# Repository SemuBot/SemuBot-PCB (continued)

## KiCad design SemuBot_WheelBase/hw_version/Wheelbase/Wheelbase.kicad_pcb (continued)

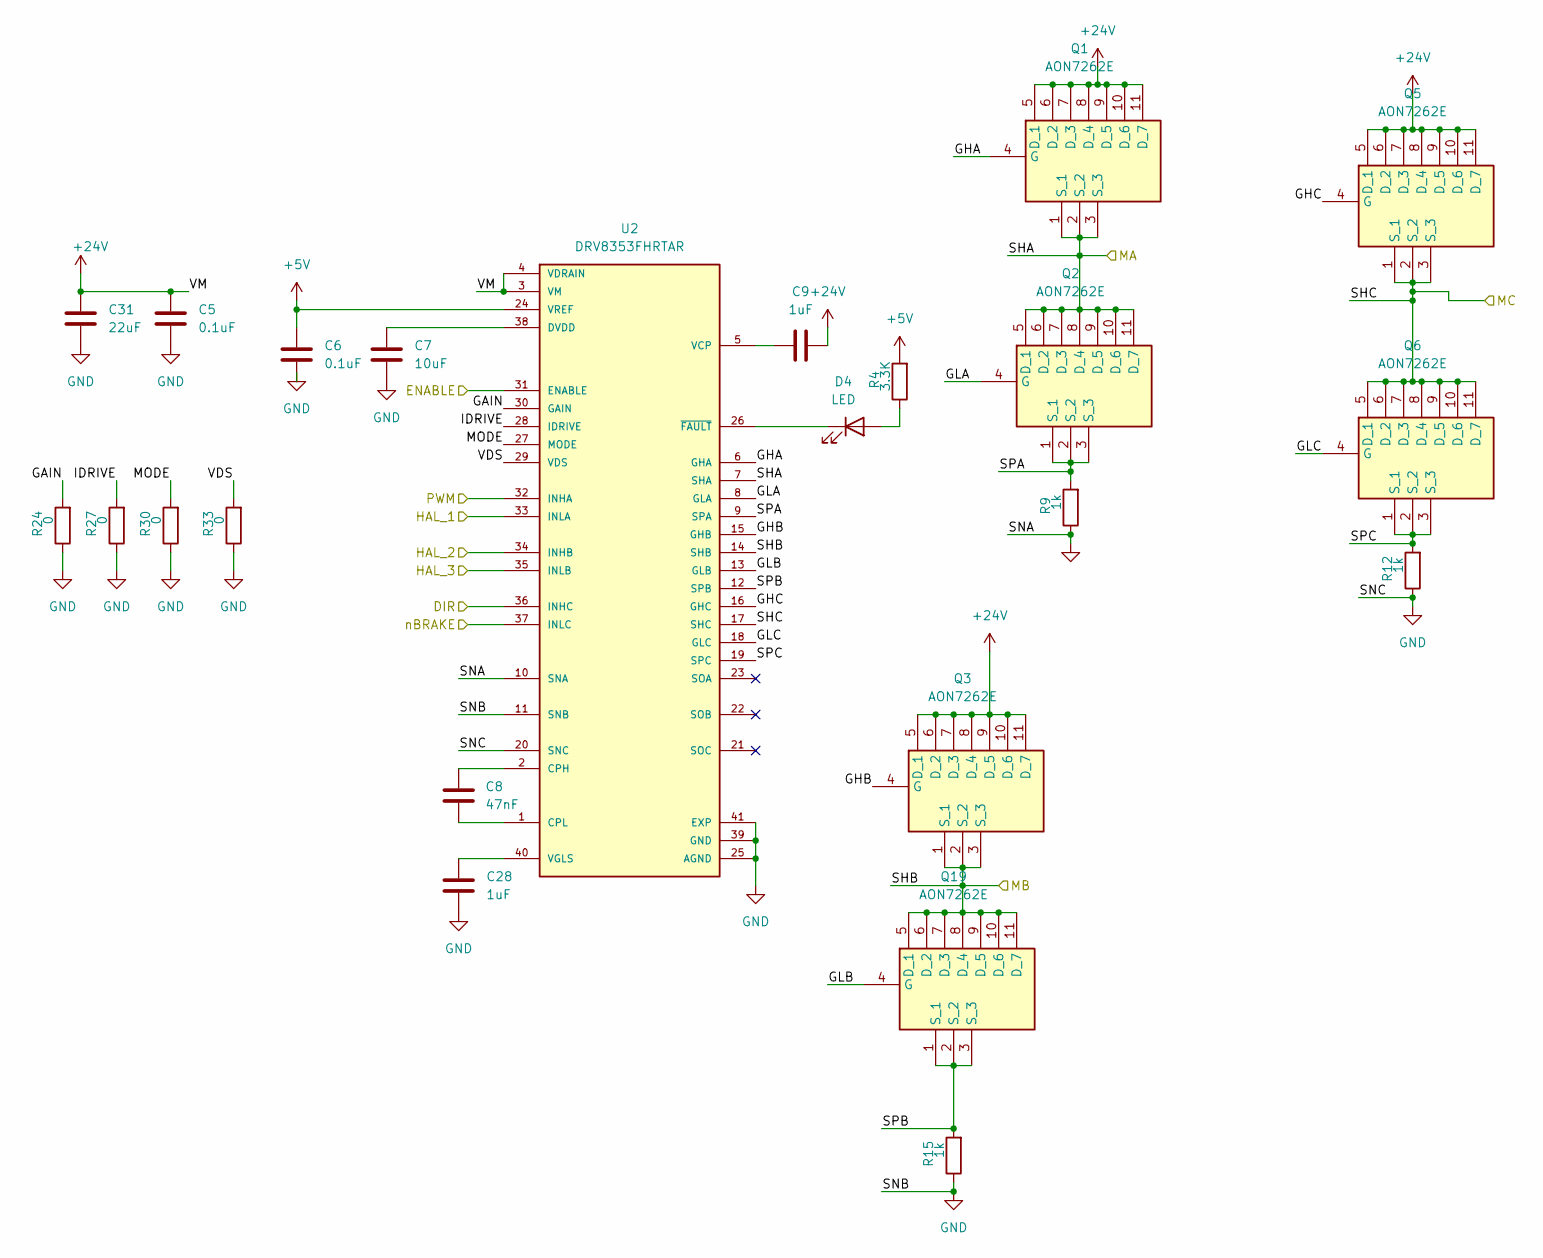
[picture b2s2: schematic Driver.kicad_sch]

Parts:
C5, C6: 0.1uF; C_0603_1608Metric_Pad1.08x0.95mm_HandSolder
C7: 10uF; C_0603_1608Metric_Pad1.08x0.95mm_HandSolder
C8: 47nF; C_0603_1608Metric_Pad1.08x0.95mm_HandSolder
C9, C28: 1uF; C_0603_1608Metric_Pad1.08x0.95mm_HandSolder
C31: 22uF; C_0805_2012Metric_Pad1.18x1.45mm_HandSolder
D4: LED; LED_0603_1608Metric_Pad1.05x0.95mm_HandSolder
Q1, Q2, Q3, Q5, Q6, Q19: AON7262E; Manufacturer_Part_Number AON7262E
R4: 3.3K; R_0603_1608Metric_Pad0.98x0.95mm_HandSolder
R9, R12, R15: 1k; R_0603_1608Metric_Pad0.98x0.95mm_HandSolder
R24, R27, R30, R33: 0; R_0603_1608Metric_Pad0.98x0.95mm_HandSolder
U2: DRV8353FHRTAR; QFN50P600X600X80-41N; PARTREV A

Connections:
+5V: C6.1, R4.2, U2.24 (VREF); also elsewhere on the board
+24V: C5.1, C9.2, C31.2, Q1.5 (D_1), Q1.6 (D_2), Q1.7 (D_3), Q1.8 (D_4), Q1.9 (D_5), Q1.10 (D_6), Q1.11 (D_7), Q3.5 (D_1), Q3.6 (D_2), Q3.7 (D_3), Q3.8 (D_4), Q3.9 (D_5), Q3.10 (D_6), Q3.11 (D_7), Q5.5 (D_1), Q5.6 (D_2), Q5.7 (D_3), Q5.8 (D_4), Q5.9 (D_5), Q5.10 (D_6), Q5.11 (D_7), U2.3 (VM), U2.4 (VDRAIN); also elsewhere on the board
/ENABLE: U2.31 (ENABLE); also elsewhere on the board
/MOTOR1_DIR: U2.36 (INHC); also elsewhere on the board
/MOTOR1_PWM: U2.32 (INHA); also elsewhere on the board
/Motor_1/GAIN: R24.2, U2.30 (GAIN)
/Motor_1/GHA: Q1.4 (G), U2.6 (GHA)
/Motor_1/GHB: Q3.4 (G), U2.15 (GHB)
/Motor_1/GHC: Q5.4 (G), U2.16 (GHC)
/Motor_1/GLA: Q2.4 (G), U2.8 (GLA)
/Motor_1/GLB: Q19.4 (G), U2.13 (GLB)
/Motor_1/GLC: Q6.4 (G), U2.18 (GLC)
/Motor_1/HAL_1: U2.33 (INLA); also elsewhere on the board
/Motor_1/HAL_2: U2.34 (INHB); also elsewhere on the board
/Motor_1/HAL_3: U2.35 (INLB); also elsewhere on the board
/Motor_1/IDRIVE: R27.2, U2.28 (IDRIVE)
/Motor_1/MODE: R30.2, U2.27 (MODE)
/Motor_1/SHA: Q1.1 (S_1), Q1.2 (S_2), Q1.3 (S_3), Q2.5 (D_1), Q2.6 (D_2), Q2.7 (D_3), Q2.8 (D_4), Q2.9 (D_5), Q2.10 (D_6), Q2.11 (D_7), U2.7 (SHA); also elsewhere on the board
/Motor_1/SHB: Q3.1 (S_1), Q3.2 (S_2), Q3.3 (S_3), Q19.5 (D_1), Q19.6 (D_2), Q19.7 (D_3), Q19.8 (D_4), Q19.9 (D_5), Q19.10 (D_6), Q19.11 (D_7), U2.14 (SHB); also elsewhere on the board
/Motor_1/SHC: Q5.1 (S_1), Q5.2 (S_2), Q5.3 (S_3), Q6.5 (D_1), Q6.6 (D_2), Q6.7 (D_3), Q6.8 (D_4), Q6.9 (D_5), Q6.10 (D_6), Q6.11 (D_7), U2.17 (SHC); also elsewhere on the board
/Motor_1/SPA: Q2.1 (S_1), Q2.2 (S_2), Q2.3 (S_3), R9.2, U2.9 (SPA)
/Motor_1/SPB: Q19.1 (S_1), Q19.2 (S_2), Q19.3 (S_3), R15.2, U2.12 (SPB)
/Motor_1/SPC: Q6.1 (S_1), Q6.2 (S_2), Q6.3 (S_3), R12.2, U2.19 (SPC)
/Motor_1/VDS: R33.2, U2.29 (VDS)
/nBRAKE: U2.37 (INLC); also elsewhere on the board
GND: C5.2, C6.2, C7.2, C28.1, C31.1, R9.1, R12.1, R15.1, R24.1, R27.1, R30.1, R33.1, U2.10 (SNA), U2.11 (SNB), U2.20 (SNC), U2.25 (AGND), U2.39 (GND), U2.41 (EXP); also elsewhere on the board
unnamed: D4.2 (A), R4.1
unnamed: D4.1 (K), U2.26 (~FAULT)
unnamed: C8.1, U2.2 (CPH)
unnamed: C8.2, U2.1 (CPL)
unnamed: C7.1, U2.38 (DVDD)
unnamed: C9.1, U2.5 (VCP)
unnamed: C28.2, U2.40 (VGLS)

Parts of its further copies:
C17, C18, C23, C24: 0.1uF; C_0603_1608Metric_Pad1.08x0.95mm_HandSolder
C19, C25: 10uF; C_0603_1608Metric_Pad1.08x0.95mm_HandSolder
C20, C26: 47nF; C_0603_1608Metric_Pad1.08x0.95mm_HandSolder
C21, C27, C29, C30: 1uF; C_0603_1608Metric_Pad1.08x0.95mm_HandSolder
C32, C33: 22uF; C_0805_2012Metric_Pad1.18x1.45mm_HandSolder
D5, D6: LED; LED_0603_1608Metric_Pad1.05x0.95mm_HandSolder
Q4, Q7, Q8, Q9, Q10, Q11, Q12, Q13, Q14, Q15, Q20, Q21: AON7262E; Manufacturer_Part_Number AON7262E
R7, R8: 3.3K; R_0603_1608Metric_Pad0.98x0.95mm_HandSolder
R10, R11, R13, R14, R16, R17: 1k; R_0603_1608Metric_Pad0.98x0.95mm_HandSolder
R25, R26, R28, R29, R31, R32, R34, R35: 0; R_0603_1608Metric_Pad0.98x0.95mm_HandSolder
U3, U4: DRV8353FHRTAR; QFN50P600X600X80-41N; PARTREV A

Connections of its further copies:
+5V: C18.1, C24.1, R7.2, R8.2, U3.24 (VREF), U4.24 (VREF); also elsewhere on the board
+24V: C17.1, C21.2, C23.1, C27.2, C32.2, C33.2, Q4.5 (D_1), Q4.6 (D_2), Q4.7 (D_3), Q4.8 (D_4), Q4.9 (D_5), Q4.10 (D_6), Q4.11 (D_7), Q7.5 (D_1), Q7.6 (D_2), Q7.7 (D_3), Q7.8 (D_4), Q7.9 (D_5), Q7.10 (D_6), Q7.11 (D_7), Q9.5 (D_1), Q9.6 (D_2), Q9.7 (D_3), Q9.8 (D_4), Q9.9 (D_5), Q9.10 (D_6), Q9.11 (D_7), Q11.5 (D_1), Q11.6 (D_2), Q11.7 (D_3), Q11.8 (D_4), Q11.9 (D_5), Q11.10 (D_6), Q11.11 (D_7), Q13.5 (D_1), Q13.6 (D_2), Q13.7 (D_3), Q13.8 (D_4), Q13.9 (D_5), Q13.10 (D_6), Q13.11 (D_7), Q15.5 (D_1), Q15.6 (D_2), Q15.7 (D_3), Q15.8 (D_4), Q15.9 (D_5), Q15.10 (D_6), Q15.11 (D_7), U3.3 (VM), U3.4 (VDRAIN), U4.3 (VM), U4.4 (VDRAIN); also elsewhere on the board
/ENABLE: U3.31 (ENABLE), U4.31 (ENABLE); also elsewhere on the board
/MOTOR2_DIR: U3.36 (INHC); also elsewhere on the board
/MOTOR2_PWM: U3.32 (INHA); also elsewhere on the board
/MOTOR3_DIR: U4.36 (INHC); also elsewhere on the board
/MOTOR3_PWM: U4.32 (INHA); also elsewhere on the board
/Motor_2/GAIN: R25.2, U3.30 (GAIN)
/Motor_2/GHA: Q7.4 (G), U3.6 (GHA)
/Motor_2/GHB: Q4.4 (G), U3.15 (GHB)
/Motor_2/GHC: Q11.4 (G), U3.16 (GHC)
/Motor_2/GLA: Q8.4 (G), U3.8 (GLA)
/Motor_2/GLB: Q20.4 (G), U3.13 (GLB)
/Motor_2/GLC: Q10.4 (G), U3.18 (GLC)
/Motor_2/HAL_1: U3.33 (INLA); also elsewhere on the board
/Motor_2/HAL_2: U3.34 (INHB); also elsewhere on the board
/Motor_2/HAL_3: U3.35 (INLB); also elsewhere on the board
/Motor_2/IDRIVE: R28.2, U3.28 (IDRIVE)
/Motor_2/MODE: R31.2, U3.27 (MODE)
/Motor_2/SHA: Q7.1 (S_1), Q7.2 (S_2), Q7.3 (S_3), Q8.5 (D_1), Q8.6 (D_2), Q8.7 (D_3), Q8.8 (D_4), Q8.9 (D_5), Q8.10 (D_6), Q8.11 (D_7), U3.7 (SHA); also elsewhere on the board
/Motor_2/SHB: Q4.1 (S_1), Q4.2 (S_2), Q4.3 (S_3), Q20.5 (D_1), Q20.6 (D_2), Q20.7 (D_3), Q20.8 (D_4), Q20.9 (D_5), Q20.10 (D_6), Q20.11 (D_7), U3.14 (SHB); also elsewhere on the board
/Motor_2/SHC: Q10.5 (D_1), Q10.6 (D_2), Q10.7 (D_3), Q10.8 (D_4), Q10.9 (D_5), Q10.10 (D_6), Q10.11 (D_7), Q11.1 (S_1), Q11.2 (S_2), Q11.3 (S_3), U3.17 (SHC); also elsewhere on the board
/Motor_2/SPA: Q8.1 (S_1), Q8.2 (S_2), Q8.3 (S_3), R10.2, U3.9 (SPA)
/Motor_2/SPB: Q20.1 (S_1), Q20.2 (S_2), Q20.3 (S_3), R16.2, U3.12 (SPB)
/Motor_2/SPC: Q10.1 (S_1), Q10.2 (S_2), Q10.3 (S_3), R13.2, U3.19 (SPC)
/Motor_2/VDS: R34.2, U3.29 (VDS)
/Motor_3/GAIN: R26.2, U4.30 (GAIN)
/Motor_3/GHA: Q13.4 (G), U4.6 (GHA)
/Motor_3/GHB: Q9.4 (G), U4.15 (GHB)
/Motor_3/GHC: Q15.4 (G), U4.16 (GHC)
/Motor_3/GLA: Q14.4 (G), U4.8 (GLA)
/Motor_3/GLB: Q21.4 (G), U4.13 (GLB)
/Motor_3/GLC: Q12.4 (G), U4.18 (GLC)
/Motor_3/HAL_1: U4.33 (INLA); also elsewhere on the board
/Motor_3/HAL_2: U4.34 (INHB); also elsewhere on the board
/Motor_3/HAL_3: U4.35 (INLB); also elsewhere on the board
/Motor_3/IDRIVE: R29.2, U4.28 (IDRIVE)
/Motor_3/MODE: R32.2, U4.27 (MODE)
/Motor_3/SHA: Q13.1 (S_1), Q13.2 (S_2), Q13.3 (S_3), Q14.5 (D_1), Q14.6 (D_2), Q14.7 (D_3), Q14.8 (D_4), Q14.9 (D_5), Q14.10 (D_6), Q14.11 (D_7), U4.7 (SHA); also elsewhere on the board
/Motor_3/SHB: Q9.1 (S_1), Q9.2 (S_2), Q9.3 (S_3), Q21.5 (D_1), Q21.6 (D_2), Q21.7 (D_3), Q21.8 (D_4), Q21.9 (D_5), Q21.10 (D_6), Q21.11 (D_7), U4.14 (SHB); also elsewhere on the board
/Motor_3/SHC: Q12.5 (D_1), Q12.6 (D_2), Q12.7 (D_3), Q12.8 (D_4), Q12.9 (D_5), Q12.10 (D_6), Q12.11 (D_7), Q15.1 (S_1), Q15.2 (S_2), Q15.3 (S_3), U4.17 (SHC); also elsewhere on the board
/Motor_3/SPA: Q14.1 (S_1), Q14.2 (S_2), Q14.3 (S_3), R11.2, U4.9 (SPA)
/Motor_3/SPB: Q21.1 (S_1), Q21.2 (S_2), Q21.3 (S_3), R17.2, U4.12 (SPB)
/Motor_3/SPC: Q12.1 (S_1), Q12.2 (S_2), Q12.3 (S_3), R14.2, U4.19 (SPC)
/Motor_3/VDS: R35.2, U4.29 (VDS)
/nBRAKE: U3.37 (INLC), U4.37 (INLC); also elsewhere on the board
GND: C17.2, C18.2, C19.2, C23.2, C24.2, C25.2, C29.1, C30.1, C32.1, C33.1, R10.1, R11.1, R13.1, R14.1, R16.1, R17.1, R25.1, R26.1, R28.1, R29.1, R31.1, R32.1, R34.1, R35.1, U3.10 (SNA), U3.11 (SNB), U3.20 (SNC), U3.25 (AGND), U3.39 (GND), U3.41 (EXP), U4.10 (SNA), U4.11 (SNB), U4.20 (SNC), U4.25 (AGND), U4.39 (GND), U4.41 (EXP); also elsewhere on the board
unnamed: D5.2 (A), R7.1
unnamed: D5.1 (K), U3.26 (~FAULT)
unnamed: D6.2 (A), R8.1
unnamed: D6.1 (K), U4.26 (~FAULT)
unnamed: C20.1, U3.2 (CPH)
unnamed: C20.2, U3.1 (CPL)
unnamed: C19.1, U3.38 (DVDD)
unnamed: C21.1, U3.5 (VCP)
unnamed: C29.2, U3.40 (VGLS)
unnamed: C26.1, U4.2 (CPH)
unnamed: C26.2, U4.1 (CPL)
unnamed: C25.1, U4.38 (DVDD)
unnamed: C27.1, U4.5 (VCP)
unnamed: C30.2, U4.40 (VGLS)

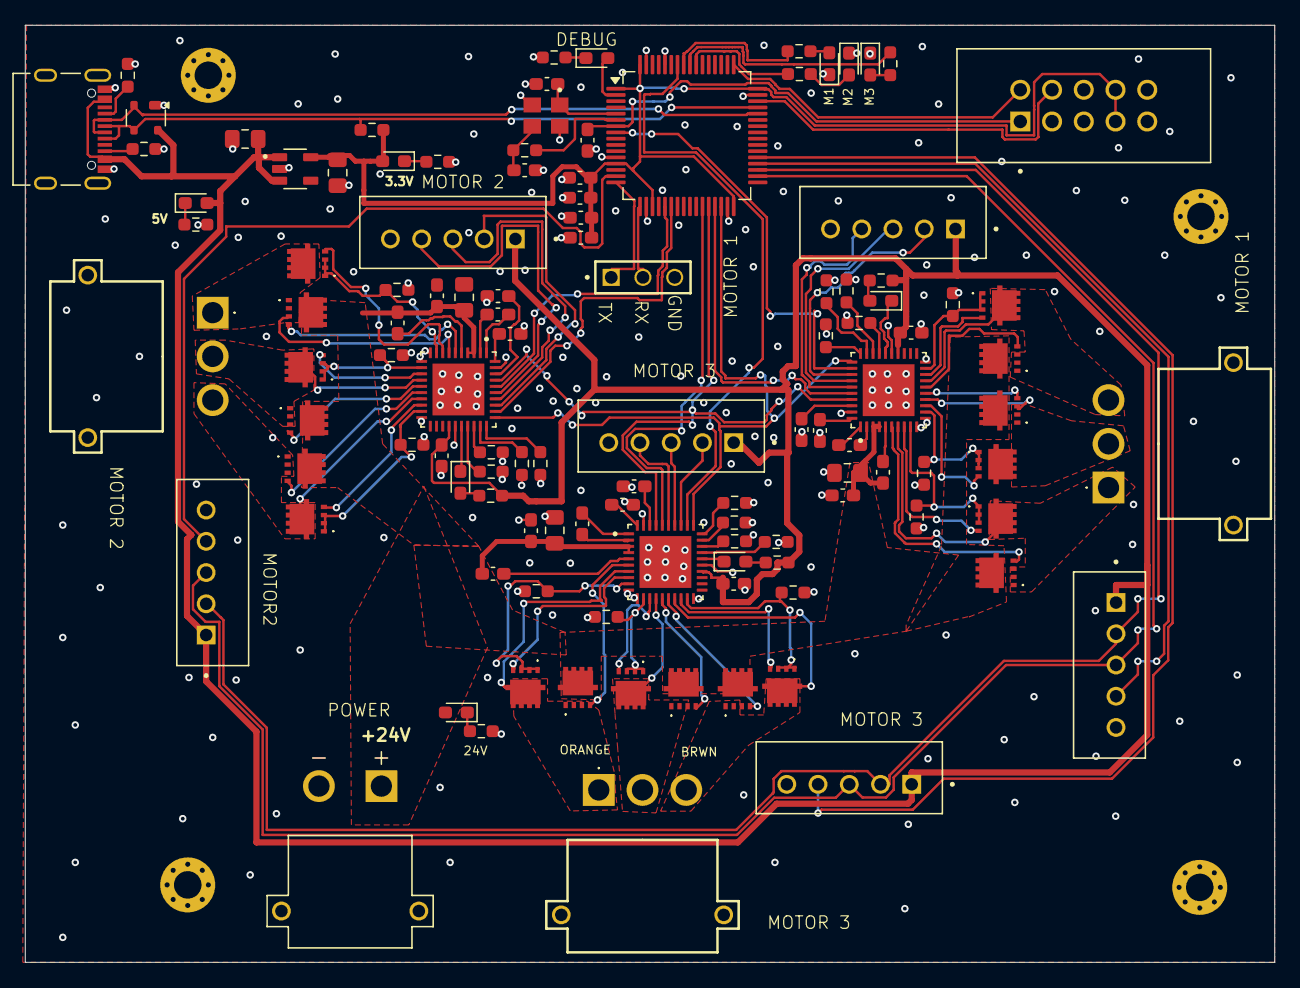
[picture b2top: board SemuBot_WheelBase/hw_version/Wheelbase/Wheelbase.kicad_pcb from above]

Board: 2 copper layers, 100.0 x 75.0 mm, 117 parts (0 on the bottom side), 118 nets.

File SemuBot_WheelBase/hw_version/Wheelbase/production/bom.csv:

Designator,Footprint,Quantity,Value,LCSC Part #
"C1, C4",0805,2,10uF,
"C10, C11",0603,2,10pF,
C12,0603,1,4.7uF,
"C13, C14, C15, C3",0603,4,100nF,
"C17, C18, C23, C24, C5, C6",0603,6,0.1uF,
"C19, C25, C7",0603,3,10uF,
"C20, C26, C8",0603,3,47nF,
"C21, C27, C28, C29, C30, C9",0603,6,1uF,
"C31, C32, C33",0805,3,22uF,
"D10, D11, D12, D2, D7, D8, D9",0603,7,red,
D3,SOT-143,1,PRTR5V0U2X,
"D4, D5, D6",0603,3,LED,
J1,AMPHENOL_10155435-00011LF,1,10155435-00011LF,
"J10, J11, J12, J4, J5, J6",JST_B5B-XH-A_LF__SN_,6,B5B-XH-A_LF__SN_,
J14,AMASS_XT30PW-M,1,XT30PW-M,
J2,SAMTEC_MTSW-103-09-L-S-400,1,MTSW-103-09-L-S-400,
"J3, J7, J8",MR30PWM,3,MR30PW-M,
J9,CONNFLY_DS1013-10SSIB1,1,DS1013-10SSIB1,
"Q1, Q10, Q11, Q12, Q13, Q14, Q15, Q19, Q2, Q20, Q21, Q3, Q4, Q5, Q6, Q7, Q8, Q9",AON7262E,18,AON7262E,
"R1, R2",0603,2,5.1K,
"R10, R11, R12, R13, R14, R15, R16, R17, R9",0603,9,1k,
"R18, R19, R20, R21, R22, R23, R4, R6, R7, R8",0603,10,3.3K,
"R24, R25, R26, R27, R28, R29, R30, R31, R32, R33, R34, R35",0603,12,0,
R36,0603,1,1.5k,
R5,0603,1,47,
U1,LQFP-64_10x10mm_P0.5mm,1,STM32F303RET6,
"U2, U3, U4",QFN50P600X600X80-41N,3,DRV8353FHRTAR,
U5,SOT94P279X129-5N,1,RT9013-33GB,
Y2,OSC_X322516MLB4SI,1,X322516MLB4SI,

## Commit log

2024-01-15 PCB and chematics initial
2024-11-29 Beginning of wheelbase pcb
2024-12-09 Snapshot
2025-01-08 Revision time
2025-01-28 Final version atm
2025-03-18 Ver2
2025-03-19 Updating board
2025-04-15 Cable connection chart added
2025-04-22 Updated cable connection chart
2025-09-06 Random push
2025-11-24 Wheelbase HW version and SPI version.
2025-11-25 SPI version
2025-12-12 SPI version update
